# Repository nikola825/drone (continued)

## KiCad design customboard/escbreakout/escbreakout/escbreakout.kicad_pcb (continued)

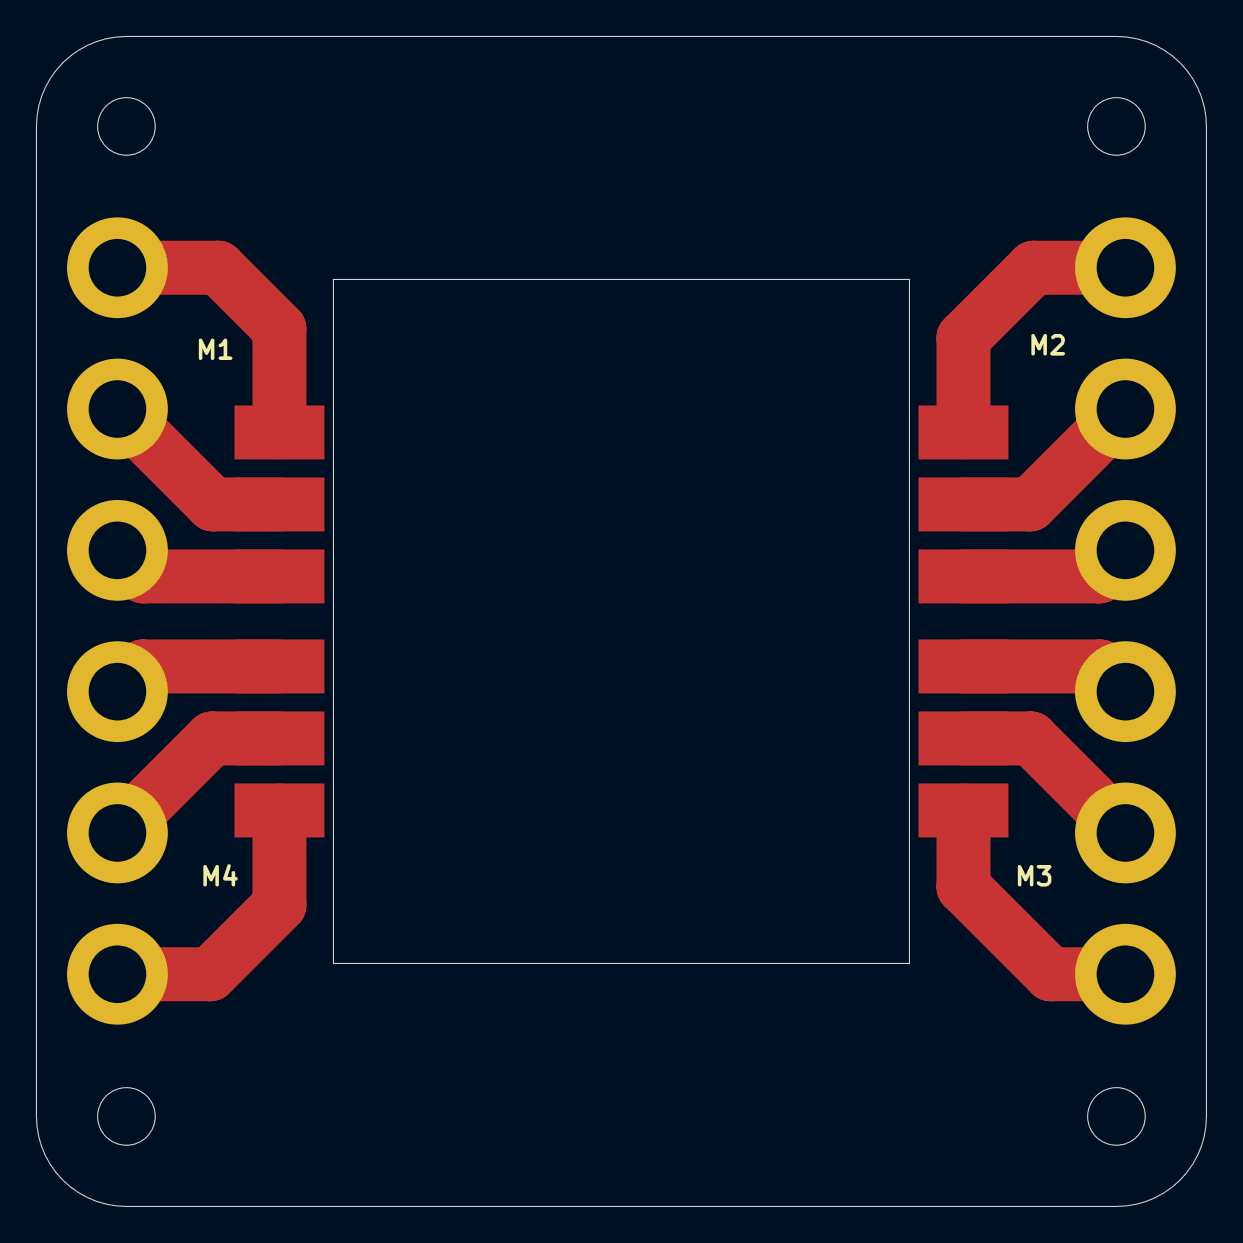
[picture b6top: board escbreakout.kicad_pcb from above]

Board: 2 copper layers, 65.0 x 65.0 mm, 28 parts (0 on the bottom side), 12 nets.

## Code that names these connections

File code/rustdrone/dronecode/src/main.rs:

#![no_std]
#![no_main]

use crsf::{crsf_receiver_task, crsf_telemetry_task, CRSFChannels};
use defmt::info;
use embassy_executor::Spawner;
use embassy_stm32::adc::{Adc, AdcChannel};
use embassy_stm32::gpio::Input;
use embassy_stm32::time::Hertz;
use embassy_stm32::{bind_interrupts, i2c, peripherals, Config};
use embassy_stm32::{
    gpio::{Level, Output, Speed},
    usart::{self},
};
use embassy_sync::lazy_lock::LazyLock;
use embassy_time::{Duration, Instant, Ticker, Timer};
use icm42688::ICM42688;
use motors::{disarm, drive, Motor, MotorsContext};
use navigation::{navigate, NavigationContext};
use storage::Store;
use {defmt_rtt as _, panic_probe as _};

mod crsf;
mod dshot;
mod icm42688;
mod motors;
mod navigation;
mod nopdelays;
mod storage;

bind_interrupts!(struct Irqs {
    USART2 => usart::InterruptHandler<peripherals::USART2>;
    I2C1_EV => i2c::EventInterruptHandler<peripherals::I2C1>;
    I2C1_ER => i2c::ErrorInterruptHandler<peripherals::I2C1>;
});

struct DroneContext {
    pub armed: bool,
    pub motor_context: MotorsContext,
    pub navigation_context: NavigationContext,
}

impl DroneContext {
    pub fn update_armed(&mut self, commands: &CRSFChannels) {
        let stay_armed = self.armed & commands.armed();
        let arm_at_zero = commands.armed() && commands.throttle() < 10;
        self.armed = commands.is_fresh() && (stay_armed || arm_at_zero);
    }
}

#[embassy_executor::main]
async fn main(_spawner: Spawner) {
    static STORE: LazyLock<Store> = LazyLock::new(|| Store::new());

    let mut config = Config::default();
    {
        use embassy_stm32::rcc::*;
        config.rcc.hse = Some(Hse {
            freq: Hertz(20_000_000),
            mode: HseMode::Oscillator,
        });
        config.rcc.pll_src = PllSource::HSE;
        config.rcc.pll = Some(Pll {
            prediv: PllPreDiv::DIV20,
            mul: PllMul::MUL400,
            divp: Some(PllPDiv::DIV4), // 20MHz / 20 * 400 / 4 = 100Mhz.
            divq: Some(PllQDiv::DIV4),
            divr: None,
        });
        config.rcc.ahb_pre = AHBPrescaler::DIV1;
        config.rcc.apb1_pre = APBPrescaler::DIV2;
        config.rcc.apb2_pre = APBPrescaler::DIV2;
        config.rcc.sys = Sysclk::PLL1_P;
    }

    let peripherals = embassy_stm32::init(config);
    let mut blue: Output = Output::new(peripherals.PA11, Level::Low, Speed::VeryHigh);
    let mut green: Output = Output::new(peripherals.PA4, Level::Low, Speed::VeryHigh);
    let mut yellow: Output = Output::new(peripherals.PA12, Level::Low, Speed::VeryHigh);

    green.set_high();

    let mut battery_adc = Adc::new(peripherals.ADC1);
    battery_adc.set_resolution(embassy_stm32::adc::Resolution::BITS12);

    let mut imu = ICM42688::new(
        peripherals.SPI3,
        peripherals.PB3,
        peripherals.PB5,
        peripherals.PB4,
        peripherals.DMA1_CH5,
        peripherals.DMA1_CH0,
        peripherals.PB9,
    );
    imu.init().await;

    yellow.set_high();

    let front_left = Motor::new(peripherals.PB0);
    let front_right = Motor::new(peripherals.PB1);
    let rear_left = Motor::new(peripherals.PA7);
    let rear_right = Motor::new(peripherals.PA6);

    Timer::after_millis(10).await;

    let (crsf_rx, crsf_tx) = crsf::make_uart_pair(
        peripherals.USART2,
        peripherals.PA3,
        peripherals.PA2,
        peripherals.DMA1_CH6,
        peripherals.DMA1_CH7,
        Irqs,
    );

    blue.set_high();

    _spawner
        .spawn(crsf_receiver_task(crsf_rx, STORE.get()))
        .unwrap();
    _spawner
        .spawn(crsf_telemetry_task(battery_adc, peripherals.PA5.degrade_adc(), crsf_tx))
        .unwrap();

    let context = DroneContext {
        armed: false,
        motor_context: MotorsContext::new(front_left, front_right, rear_left, rear_right),
        navigation_context: NavigationContext::new(),
    };
    _spawner
        .spawn(tick_task(blue, green, yellow, imu, context, STORE.get()))
        .unwrap();
}

#[embassy_executor::task]
async fn tick_task(
    mut blue_led: Output<'static>,
    mut green_led: Output<'static>,
    mut yellow_led: Output<'static>,
    mut imu: ICM42688,
    mut context: DroneContext,
    store: &'static Store,
) {
    const PID_PERIOD_US: u64 = 500;
    let mut ticker = Ticker::every(Duration::from_micros(PID_PERIOD_US));
    let mut x = 0;

    blue_led.set_low();
    green_led.set_low();
    yellow_led.set_high();

    let mut duration = 0f32;
    loop {
        let t1 = Instant::now();
        let snapshot = store.snapshot().await;

        context.update_armed(&snapshot.channels);

        green_led.set_level(match context.armed {
            true => Level::High,
            false => Level::Low,
        });

        yellow_led.set_level(match context.armed {
            true => Level::Low,
            false => Level::High,
        });

        blue_led.set_level(match snapshot.channels.is_fresh() {
            true => Level::High,
            false => Level::Low,
        });

        navigate(&mut imu, &mut context, &snapshot.channels);

        if context.armed {
            drive(&mut context);
        } else {
            disarm(&mut context).await;
        }

        let t2 = Instant::now();

        duration = (t2 - t1).as_micros() as f32 * 0.5 + duration * 0.5;
        x = x + 1;
        if x > 800 * (1000 / PID_PERIOD_US) {
            x = 0;
            info!("TICK {}", duration);
        }

        ticker.next().await;
    }
}

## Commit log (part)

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2023-04-05 initial:
2023-04-05 commit2
2023-05-05 migrate to CLion
2023-05-27 motor controll and stopping
2023-08-05 basic control done, starting work on MPU
2023-08-09 yaw PID setup, angle rollover
2023-08-11 roll/pitch pid, watchdog
2023-08-11 Wire timeout, motor watchdog
2023-08-11 fixes
2023-08-27 BNO055
2023-08-27 mpuholder
2023-08-28 orient
2023-08-29 BNO last
2023-08-31 MPU gyroonly
2023-09-02 final
2023-09-04 IMU angle
2024-09-11 V2: dshot, rigid body, onboard MPU
2024-09-11 V3 initial
2024-09-12 stuff
2024-09-22 ELRS joystick, locking
2024-09-22 rust LSP
2024-09-23 rust CRSF
2024-10-12 V3 first flight
2024-10-18 filtering, battery with vref, camera mounting
2024-10-18 new embassy
2024-10-24 whole model visible, faster rates, battery voltage smoothing
2024-10-26 voltage round instead of trunc
2024-11-02 motor cleanup
2024-11-02 cleanup
2024-11-02 more cleanup
2024-11-02 STLs
2024-11-02 complete fix
2024-11-02 Create LICENSE
2024-11-08 motor reset process
2024-11-09 motor refactor
2024-11-18 adjustable pids; faster dshots; beeping; minor refactor
2024-11-19 compiler optimizations
2024-11-19 remove unncessary dependencies
2024-11-19 Update code readme
2024-11-21 motor reset code
2024-11-21 stm32f7 initial work
2024-11-21 Describe other branches
2024-11-23 usb implementation start
2024-11-25 h7 initial
2024-11-25 usb bom
2024-11-25 h7 routing
2024-11-26 h7 board almost full
2024-12-14 h7 board work
2024-12-30 USB variant
2024-12-30 Minor 3DP improvements
2024-12-30 CRSF err logging
2024-12-30 usb logic minor refactor
2024-12-31 stm32h7 board
2024-12-31 conditional compilation
2024-12-31 board work
2025-01-04 h7 hardware done
2025-01-26 h7 basic work done, antenna hole on top
2025-01-27 smps initial
2025-01-27 smps complete
2025-02-03 reduce kd range, add D term low-pass filter
2025-02-03 smps pcb; bom
2025-02-03 h7 hw_select cleanup
2025-02-03 cleanup and fixes
2025-02-03 [wip] dshot parallel hackery
2025-04-18 kicad update
2025-04-18 msp cleanup
2025-04-18 simplified dshot
2025-04-18 minor fixes
2025-04-18 battery/telemetry separation, parallel dshot, wider pin headers
2025-04-18 dependency cleanup
2025-04-18 msp impl
2025-04-18 typo mess fix
2025-04-18 msp refactoring
2025-04-18 h723 further work
2025-04-18 SMA TOP; 20mm VTX; 3A SMPS; MSP OSD
2025-04-18 minor refactors
2025-04-18 msp sticks, minor refactoring
2025-04-18 expo rates, channel mapping refactor
2025-04-18 crate updates, minor refactoring
2025-04-18 link state monitoring
2025-04-18 remove vendored embassy
2025-04-21 reorganize arming logic
2025-04-26 switch to hsi
2025-04-27 recalibrate gyro for h7
2025-04-27 cortex m7
2025-04-28 minor refactorings
2025-04-28 743 further work
2025-04-28 move mcu
2025-04-28 rebase
2025-05-12 prioritize PID loop task; enable cache on h7
2025-05-14 Flash config storage on H7
2025-05-15 optimize memory organization on h7; do flash erasure before storing settings
2025-05-15 implement support for gps and cabling for it on the frame
2025-05-20 fixed d-term; throttle limit on potentiometer
2025-05-26 angle mode; align gyro to controls
2025-06-27 bga mcu
2025-06-27 UBX gps receive, show gps on msp, send gps over telemetry
2025-07-04 better gps mount, number2string fixes
2025-07-05 fix ordering of lat/lon in nav-pvt ubx packet
2025-07-06 remove old msp osd
2025-07-19 pause icache during dshot bitbanging
2025-07-19 msp show distance to home, minor cleanup
2025-07-19 gps mount on frame, frame stls cleanup
2025-08-11 H743 bga drone board Hardware: - switchable VTX power - BGA MCU - 6S support
    Code:
    - refactor calibration logic
2025-08-11 hardware selection refactor
2025-08-15 hardware selection refactoring
2025-09-21 HAL fixes, remove 5V diode
2025-09-21 pmos vtx power switching initial
2025-09-30 pmos vtx sch
2025-10-03 7inch initial implementation
2025-10-03 add 7 inch frame
2025-10-05 Arm tolerance fixes
2025-10-06 adjust dshot timings to work on blheli_s as well; do parallel setting of directions
2025-10-18 seven inch PID values update
2025-10-19 embassy update
2025-10-28 7inch gps plate, whole assembly
2025-10-29 relative home heading; cell detection; refactoring
2025-10-29 limit slice indexing in msp osd
2025-11-03 esc initial attempt
2025-11-13 esc 4x
2025-11-13 lb reorg
2025-11-17 4x done
2025-11-17 footprint fixes
2025-11-19 power board done, minor fixes in logic board
2025-12-04 4x esc fixes
2025-12-08 sot-89 regulator
2025-12-08 logic board 3v3 split
2025-12-16 narrower castelations on logic board; proper stls
2026-01-08 fixed wing servo support, generic mixes
2026-01-21 five inch leg fix
2026-01-21 five inch leg fix part 2
2026-03-17 support for servos and wing layout
2026-03-17 Implement 1x esc. Reorganize hardware folder
2026-03-18 angle mode yaw fix, pre-arm logic
2026-03-24 stuff wip
2026-04-26 stored config error log improvements
2026-04-26 4X ESC
2026-04-26 Wider ESC battery holes
2026-04-29 ESC readme
2026-05-04 high side pmos VTX switch
2026-05-10 Ignore KiCad history folders
2026-05-25 thermal vias fix
2026-06-16 MSP passthrough implementation
2026-06-27 configurator
